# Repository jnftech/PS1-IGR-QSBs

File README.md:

## Playstation 1 In-Game Reset (IGR)
### QSBs for One-wire Controller-PCB installs
<br/>
<br/>

These boards are variations on [PyroESP's](https://github.com/pyroesp) Playstation 1 Reset Mod project.

The original project and code can be found at https://github.com/pyroesp/PlayStation-1-Reset-Mod

To simplify the goal of this project: When installed into a Playstation 1 system, it facilitates a reset of the system using a button combination on controller 1, by tapping into the controller signals and toggling the system reset line. This is useful for those that have ODEs installed, as you can reset back to the menu of the ODE from the controller instead of getting up to hold the reset button down.

Originally I had posted a variation that was more or less a shrink of their original PCB (which used a SOIC package for the microcontroller), but using the TSSOP version instead, to get the board as small as it could be for S&Gs and more of a "hardmode" install. This version of the project (while deprecated, unless you REALLY need to avoid installing to the controller PCB) is still hosted in the repository.

A while back (2022? Yes it has taken me that long to publish the final versions here) a member of the [Consolemods.org](https://www.consolemods.org) discord observed a variation on OSHpark that installed to the back of the controller PCB behind the player 1 port. However the project was not laid out correctly, thus the wrong (higher) voltage was applied to the microcontroller. This style of board is a "Quick Solder Board" (QSB), where the board is designed to sit on top of another PCB and solder directly to signal points (versus running a wire for each signal). Such a solution allows for a "one-wire" install of this project. All but one of the signals needed are available from the solder points of the controller ports themselves. The only wire that must be run is for the reset signal.
While these controller-PCB-mounted solutions were not uncommon at the time, the project on OSHpark appeared to be the only published gerbers for folks that prefer to fabricate their own PCBs.
I decided to revisit the project to produce a correctly-wired version, using my own consoles for measurement. Some earlier versions of the gerbers were posted to the discord for members to use. This respository has three variations depending on your soldering preferences. Difficulty ratings for assembling the board by hand is listed with each :)
  
Code, details of the solution, original PCB design, and instructions for programming and installation are available at [pyroesp's Github](https://github.com/pyroesp). Programming-ready hex file in the [releases section](https://github.com/pyroesp/PlayStation-1-Reset-Mod/releases)

</br></br></br>

### Controller-port (Port 1) install, SOIC Package [(OSHpark)](https://oshpark.com/shared_projects/fwJTyytg)
Assembly difficulty: Normal

This variant more or less aimed to substitute the faulty one on OSHpark. Installs over the solder points for controller port 1 and uses the SOIC package of the microcontroller (MCU). This should be fairly easy to assemble for anyone with decent soldering skills.

</br></br>

### Controller-port (Port 1) install, TSSOP Package [(OSHpark)](https://oshpark.com/shared_projects/G71d1amG)
Assembly difficulty: Hard~er

This is almost identical to the above variant, and installs the exact same way. The only difference is the use of the TSSOP package for the MCU. This requires slightly tighter soldering skills.

</br></br>

### Controller-ribbon connector (Center of controller PCB) install, UQFN Package. [(OSHpark)](https://oshpark.com/shared_projects/B2ZQAGCg)
Assembly difficulty: Ultrahard

Staying in the same spirit as my original visit to the project, this board aims to be as small is it can be. I realized that another spot on the controller PCB contained all the same signals as the controller port: The connector for the ribbon cable that connects the controller assembly to the main system board. This PCB installs to the back of that connector instead of the controller port. Continuing with that same spirit, I figured go all out and use the UQFN package of the MCU - which is the smallest package it comes in. However this means this board is significantly more difficult to assemble by hand. Not impossible - I hand assembled the one installed in my main console - but takes very good soldering skills and tools. I imagine this is the smallest "one-wire" install of this solution available. All that said, the actual installation of the board into the console should not be much more difficult than the other two options.

</br></br>

### PSone install, Flex PCB, UQFN Package *BETA*
Assembly difficulty: Ultrahard

Info coming soon!
(Quick note for anyone that wants to try this one before I get around to filling in more details - this is intended to be a flex PCB to keep it as thin as possible (flex is 0.10mm - 0.12mm) and fit under the bottom RF shield. Put kapton tape over it after installation to keep it from touching the RF shield. I have tested this install on a PSone and it works as intended. Normal PCBs are likely too thick, though I have not tried this myself. Perhaps if the RF shield is cut or omitted a regular PCB would fit. i would still go as thin as possible, for example the 0.8mm on Oshpark. Though until I provide more detailed instructions, you will have to find the reset line on the PSone yourself, or look around online. I found a good spot from the PSone service manual.)

</br></br></br></br>

### BOM:

Only two components are needed:

**U1**<br/> Depending on which board you which to assemble, the part number for the MCU will differ slightly (only the last two characters of the part number matter in this case)
- SOIC: Microchip PIC16F18325-I/SL. [Digikey](https://www.digikey.com/en/products/detail/microchip-technology/PIC16F18325-I-SL/5323625)
- TSSOP: Microchip PIC16F18325-I/ST. [Digikey](https://www.digikey.com/en/products/detail/microchip-technology/PIC16F18325-I-ST/5323626)
- UQFN: Microchip PIC16F18325-I/JQ. [Digikey](https://www.digikey.com/en/products/detail/microchip-technology/PIC16F18325-I-JQ/5639473)

**C1**:<br/>You really don't need to be picky about this part. Any 100nf to 1000nf/1uf 0603-sized Ceramic capacitor rated at 16v or above will work. <br />
    Examples:<br />
        [Samsung CL10B104KB8NNNL](https://www.digikey.com/en/products/detail/samsung-electro-mechanics/CL10B104KB8NNNL/3894274)<br />
        [Murata GCJ188R71E104KA12D](https://www.digikey.com/en/products/detail/murata-electronics/GCJ188R71E104KA12D/7363221)

### Installation Notes:
- To completely remove the chance of shorts between the IGR board and any shielding it may come in contact with, place a piece of electrical tape over the board once installed, OR place electrical tape over the sheilding area it may come in contact with. I will add a photo of this at some point.

### Fabrication Notes:
- These boards benefit from being as thin as possible, due to being positioned between the controller PCB and the metal shielding between it and the rest of the casing. The default 1.6mm PCB thinckness may be a little tight, so it's recommended to go with 0.8mm thickness. If using OSHpark, an 0.8mm width option is available at checkout. Other fabs should have a similar thickness option, even thinner in some cases.
- The text in the bottom copper layer *may* cause some fabs to complain about the size of the text. OSHpark doesnt have an issue (they seem to fab whatever you throw at them, regardless if it comes out well in the final product), but I have experienced cases in the past where JLCPCB will remove any text from the board that they deem too small.
- There are other variants of the MCU you can use, depending on whether you have trouble sourcing the above (I did when I built my prototypes) but they may be a few cents more expensive as they have extra features or tolerances. In this project, they will all function identically:
  - The "I/" in the part number can be swapped with the "E/" variant. The latter is just "Extended Tempurature range"
  - This project uses the PIC16F18325 MCU, however the the PIC16F18**326** can also be used. It's the exact same MCU with a little bit more memory and storage. Same HEX file can be used to program either. The board I installed in my main console uses the PIC16F18326-E/JQ part. While the size of the code is fairly small, the next MCU down in the list (324) CANNOT be used as it lacks the dual SPI capability of the 325 and 326 (which this project requires).
- You will of course need a programmer to flash the code to the microcontroller, such as a PICkit3. This can be done in several ways:
  - The ICSP pads on board by soldering some temporary wiring to connect it to the programmer.
  - The ICSP pads by using a 2mm pitch pogo-pin PCB clamp such as this one on [Aliexpress](https://www.aliexpress.com/i/3256806664884457.html)
  - An alternative would be a DIP socket adapter ([an example of such on Aliexpress](https://www.aliexpress.com/item/32868905130.html)) to house the chip for programming before it is soldered to the board.

### Other Notes:
- These have not been designed with the PSone in mind, and are only tested on the original "phat" models. While the PSones have no good ODE option yet (where this mod is most useful), I have a variation in beta that I will be testing in the next few weeks.

### Tools used for this project:
- Tracespace View (SVG conversions of gerbers for the above images) https://tracespace.io/view/
- KiCad 8.0.6 https://www.kicad.org/
- GIMP for some of the image edits.
- Inkscape for some vector image edits.

### To-do
- Post more detailed installation instructions
- Post or link to reset line points for various motherboard revisions.

### License:
This derivative work maintains the same source license as the original board and project:  
Attribution-ShareAlike 4.0 International. See license file for more info

<br/><br/><br/><br/>

#
<p align="right"><sup>Enjoy some pretty renders as I learn how to use blender for "product photos"</sup></p>

<br/>

<br/><br/>

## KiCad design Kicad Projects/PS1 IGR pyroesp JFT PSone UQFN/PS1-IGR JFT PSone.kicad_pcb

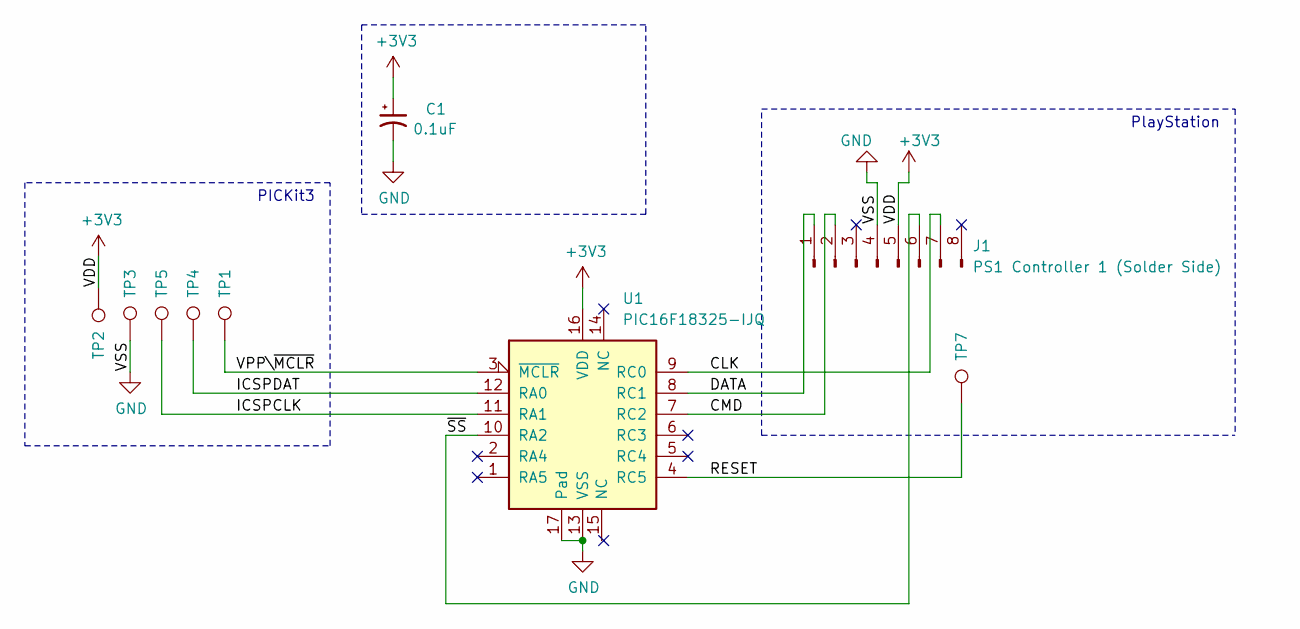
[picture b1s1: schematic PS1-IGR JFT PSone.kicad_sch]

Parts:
C1: 0.1uF; R_0603_0.8mm
J1: PS1 Controller 1 (Solder Side); PS1ControllerPort_SolderSide_1gnd0hv
TP1: VPP; TestPoint_Pad_NoSilk_D1.0mm
TP2: VDD; TestPoint_Pad_NoSilk_D1.0mm
TP3: VSS; TestPoint_Pad_NoSilk_D1.0mm
TP4: DAT; TestPoint_Pad_NoSilk_D1.0mm
TP5: CLK; TestPoint_Pad_NoSilk_D1.0mm
TP7: RST; Wirepad-2.54mm
U1: PIC16F18325-IJQ; UQFN-16-1EP_4x4mm_P0.65mm_EP2.6x2.6mm

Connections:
+3V3: C1.1, J1.5, TP2.1, U1.16 (VDD)
/CLK: J1.7, U1.9 (RC0)
/CMD: J1.2, U1.7 (RC2)
/DATA: J1.1, U1.8 (RC1)
/ICSPCLK: TP5.1, U1.11 (RA1)
/ICSPDAT: TP4.1, U1.12 (RA0)
/RESET: TP7.1, U1.4 (RC5)
/VPP\~MCLR: TP1.1, U1.3 (~MCLR)
/~SS: J1.6, U1.10 (RA2)
GND: C1.2, J1.4, TP3.1, U1.13 (VSS), U1.17 (Pad)

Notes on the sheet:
PICKit3
PlayStation

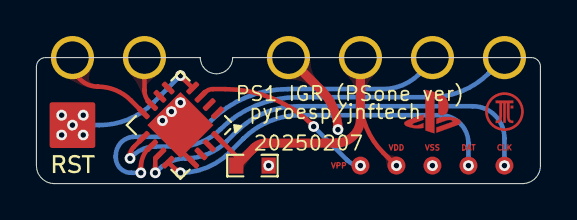
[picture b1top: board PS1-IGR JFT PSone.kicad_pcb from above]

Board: 2 copper layers, 28.0 x 7.0 mm, 9 parts (0 on the bottom side), 10 nets.

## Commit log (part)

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2025-07-30 Update README.md
    Flex PSone info quick update
